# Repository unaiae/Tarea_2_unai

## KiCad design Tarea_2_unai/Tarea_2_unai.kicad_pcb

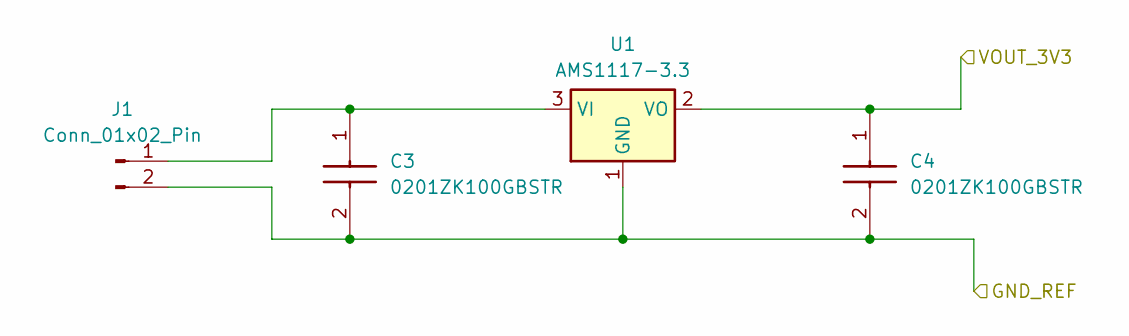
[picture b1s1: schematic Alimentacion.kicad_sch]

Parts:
C3, C4: 0201ZK100GBSTR; CAPC0603X28N; Manufacturer_Part_Number 0201ZK100GBSTR; Mouser Part Number 581-0201ZK100GBSTR
J1: Conn_01x02_Pin; PinHeader_1x04_P2.54mm_Vertical
U1: AMS1117-3.3; SOT-223-3_TabPin2

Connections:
/Alimentacion/GND_REF: C3.2, C4.2, J1.2, U1.1 (GND); also elsewhere on the board
/Alimentacion/VOUT_3V3: C4.1, U1.2 (VO); also elsewhere on the board
unnamed: C3.1, J1.1, U1.3 (VI)

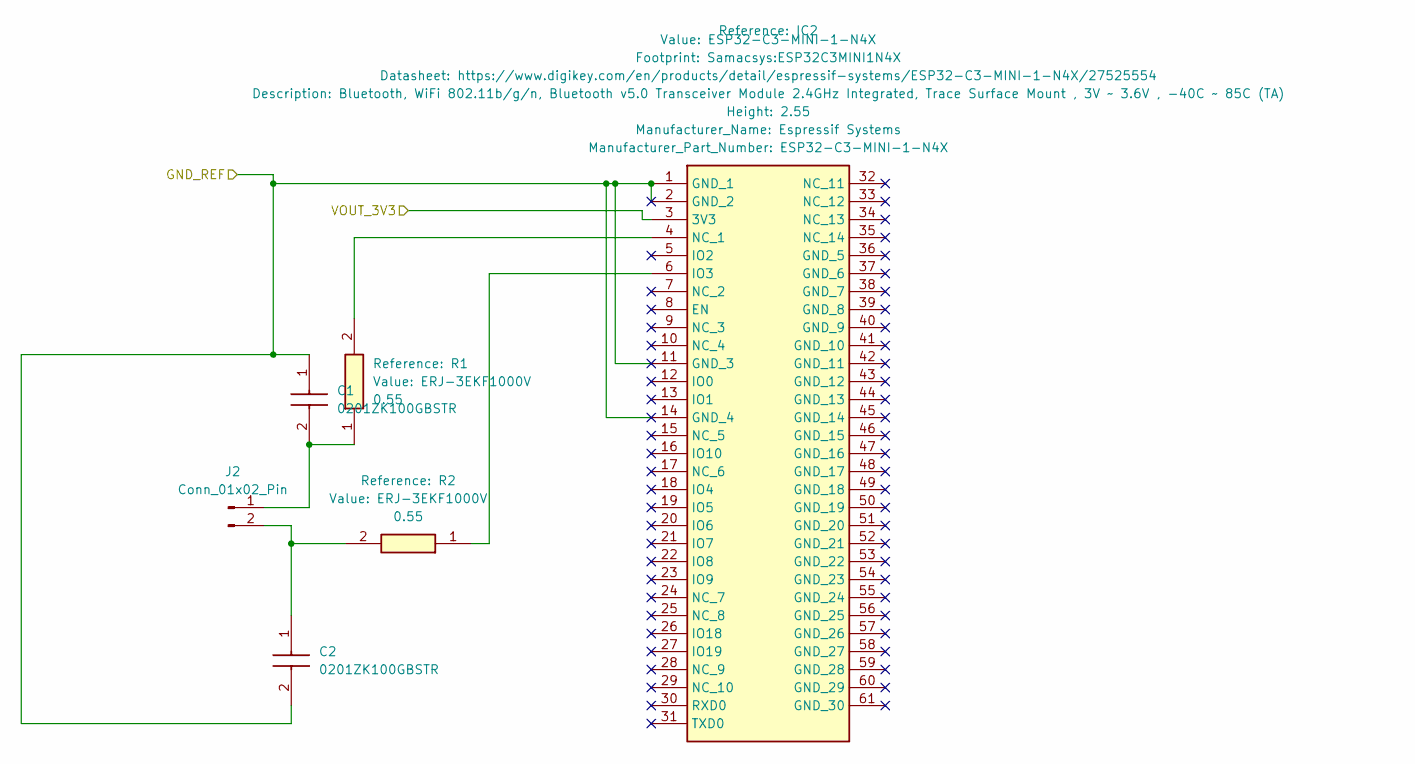
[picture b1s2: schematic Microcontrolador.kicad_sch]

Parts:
C1, C2: 0201ZK100GBSTR; CAPC0603X28N; Manufacturer_Part_Number 0201ZK100GBSTR; Mouser Part Number 581-0201ZK100GBSTR
IC2: ESP32-C3-MINI-1-N4X; ESP32C3MINI1N4X; Manufacturer_Part_Number ESP32-C3-MINI-1-N4X
J2: Conn_01x02_Pin; PinHeader_1x04_P2.54mm_Vertical
R1, R2: ERJ-3EKF1000V; RESC1608X55N; Manufacturer_Part_Number ERJ-3EKF1000V; Mouser Part Number 667-ERJ-3EKF1000V

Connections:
/Alimentacion/GND_REF: C1.1, C2.2, IC2.1 (GND_1), IC2.2 (GND_2), IC2.11 (GND_3), IC2.14 (GND_4); also elsewhere on the board
/Alimentacion/VOUT_3V3: IC2.3 (3V3); also elsewhere on the board
unnamed: IC2.6 (IO3), R2.1
unnamed: IC2.4 (NC_1), R1.2
unnamed: C1.2, J2.1, R1.1
unnamed: C2.1, J2.2, R2.2

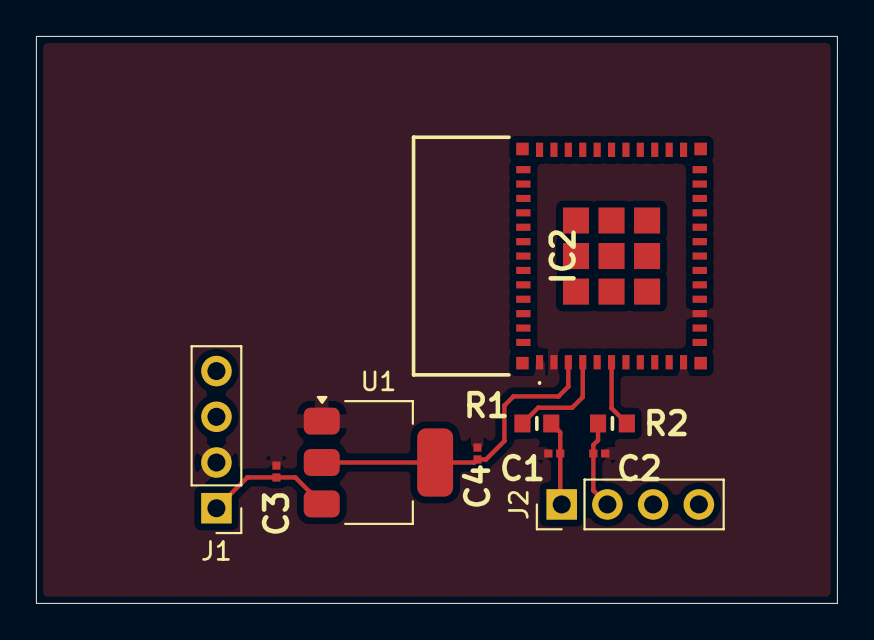
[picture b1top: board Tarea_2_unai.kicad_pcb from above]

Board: 2 copper layers, 44.5 x 31.5 mm, 10 parts (0 on the bottom side), 7 nets.
